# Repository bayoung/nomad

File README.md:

# Nomad

Keyboard for Digital Nomads

# Config and Build Firmware

* cd nomad
* git clone git@github.com:bayoung/qmk_firmware.git
* git checkout brian.young/nomad
* cd qmk_firmware
* git submodule sync --recursive
* git submodule update --init --recursive --progress
* make nomad:default
* run teensy.app
* select qmk_firmware/nomad_default.hex
* press reset on Keyboard (or Fn-Esc if there's good firmware running)
* load
* replug USB cable on keyboard

# PCB

* cd pcb
* git clone git@github.com:keebio/Keebio-Parts.pretty.git
* cd Keebio-Parts.pretty
* git checkout aec652e40624d7872b2659f307ac483922ba315f
* cd ..
* git clone git@github.com:XenGi/teensy_library.git
* git checkout 14f5629c7d822ed95580319626f745de2a11fefd
* cd ..
* open NomadLeft / NomadRight in KiCad

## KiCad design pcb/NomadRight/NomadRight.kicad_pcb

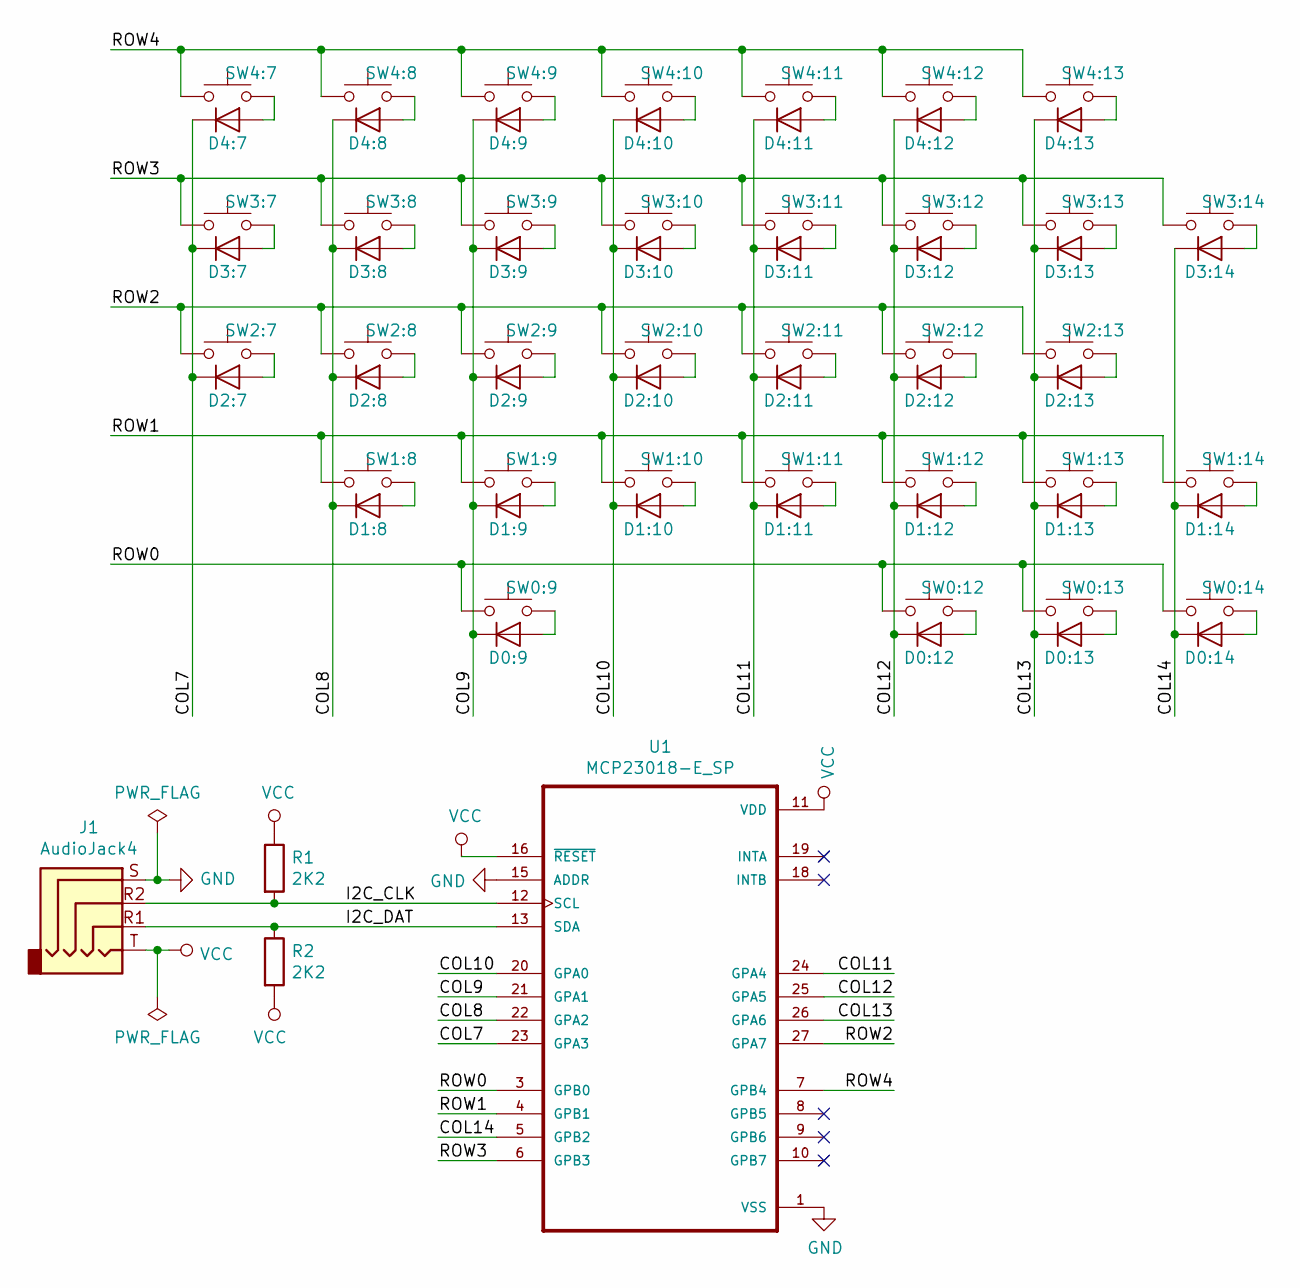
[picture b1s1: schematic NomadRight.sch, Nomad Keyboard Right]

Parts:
D0:9, D0:12, D0:13, D0:14, D1:8, D1:9, D1:10, D1:11, D1:12, D1:13, D1:14, D2:7, D2:8, D2:9, D2:10, D2:11, D2:12, D2:13, D3:7, D3:8, D3:9, D3:10, D3:11, D3:12, D3:13, D3:14, D4:7, D4:8, D4:9, D4:10, D4:11, D4:12, D4:13: 1N4148TR; D_DO-35_SOD27_P7.62mm_Horizontal
J1: AudioJack4; CUI_SJ-43514
R1, R2: 2K2; R_0805_2012Metric_Pad1.15x1.40mm_HandSolder
SW0:9, SW0:12, SW0:13, SW0:14, SW1:8, SW1:9, SW1:10, SW1:11, SW1:12, SW1:13, SW1:14, SW2:7, SW2:8, SW2:9, SW2:10, SW2:11, SW2:12, SW2:13, SW3:7, SW3:8, SW3:9, SW3:10, SW3:11, SW3:12, SW3:13, SW3:14, SW4:7, SW4:8, SW4:9, SW4:10, SW4:11, SW4:12, SW4:13: SW_Push; Kailh-PG1350-1u
U1: MCP23018-E_SP; DIP-28_W7.62mm

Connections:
/COL7: D2:7.1 (K), D3:7.1 (K), D4:7.1 (K), U1.23 (GPA3)
/COL8: D1:8.1 (K), D2:8.1 (K), D3:8.1 (K), D4:8.1 (K), U1.22 (GPA2)
/COL9: D0:9.1 (K), D1:9.1 (K), D2:9.1 (K), D3:9.1 (K), D4:9.1 (K), U1.21 (GPA1)
/COL10: D1:10.1 (K), D2:10.1 (K), D3:10.1 (K), D4:10.1 (K), U1.20 (GPA0)
/COL11: D1:11.1 (K), D2:11.1 (K), D3:11.1 (K), D4:11.1 (K), U1.24 (GPA4)
/COL12: D0:12.1 (K), D1:12.1 (K), D2:12.1 (K), D3:12.1 (K), D4:12.1 (K), U1.25 (GPA5)
/COL13: D0:13.1 (K), D1:13.1 (K), D2:13.1 (K), D3:13.1 (K), D4:13.1 (K), U1.26 (GPA6)
/COL14: D0:14.1 (K), D1:14.1 (K), D3:14.1 (K), U1.5 (GPB2)
/I2C_CLK: J1.R2, R1.2, U1.12 (SCL)
/I2C_DAT: J1.R1, R2.1, U1.13 (SDA)
/ROW0: SW0:9.1, SW0:12.1, SW0:13.1, SW0:14.1, U1.3 (GPB0)
/ROW1: SW1:8.1, SW1:9.1, SW1:10.1, SW1:11.1, SW1:12.1, SW1:13.1, SW1:14.1, U1.4 (GPB1)
/ROW2: SW2:7.1, SW2:8.1, SW2:9.1, SW2:10.1, SW2:11.1, SW2:12.1, SW2:13.1, U1.27 (GPA7)
/ROW3: SW3:7.1, SW3:8.1, SW3:9.1, SW3:10.1, SW3:11.1, SW3:12.1, SW3:13.1, SW3:14.1, U1.6 (GPB3)
/ROW4: SW4:7.1, SW4:8.1, SW4:9.1, SW4:10.1, SW4:11.1, SW4:12.1, SW4:13.1, U1.7 (GPB4)
GND: J1.S, U1.1 (VSS), U1.15 (ADDR)
unnamed: D0:9.2 (A), SW0:9.2
unnamed: D0:12.2 (A), SW0:12.2
unnamed: D0:13.2 (A), SW0:13.2
unnamed: D0:14.2 (A), SW0:14.2
unnamed: D1:8.2 (A), SW1:8.2
unnamed: D1:9.2 (A), SW1:9.2
unnamed: D1:10.2 (A), SW1:10.2
unnamed: D1:11.2 (A), SW1:11.2
unnamed: D1:12.2 (A), SW1:12.2
unnamed: D1:13.2 (A), SW1:13.2
unnamed: D1:14.2 (A), SW1:14.2
unnamed: D2:7.2 (A), SW2:7.2
unnamed: D2:8.2 (A), SW2:8.2
unnamed: D2:9.2 (A), SW2:9.2
unnamed: D2:10.2 (A), SW2:10.2
unnamed: D2:11.2 (A), SW2:11.2
unnamed: D2:12.2 (A), SW2:12.2
unnamed: D2:13.2 (A), SW2:13.2
unnamed: D3:7.2 (A), SW3:7.2
unnamed: D3:8.2 (A), SW3:8.2
unnamed: D3:9.2 (A), SW3:9.2
unnamed: D3:10.2 (A), SW3:10.2
unnamed: D3:11.2 (A), SW3:11.2
unnamed: D3:12.2 (A), SW3:12.2
unnamed: D3:13.2 (A), SW3:13.2
unnamed: D3:14.2 (A), SW3:14.2
unnamed: D4:7.2 (A), SW4:7.2
unnamed: D4:8.2 (A), SW4:8.2
unnamed: D4:9.2 (A), SW4:9.2
unnamed: D4:10.2 (A), SW4:10.2
unnamed: D4:11.2 (A), SW4:11.2
unnamed: D4:12.2 (A), SW4:12.2
unnamed: D4:13.2 (A), SW4:13.2
VCC: J1.T, R1.1, R2.2, U1.11 (VDD), U1.16 (~RESET~)

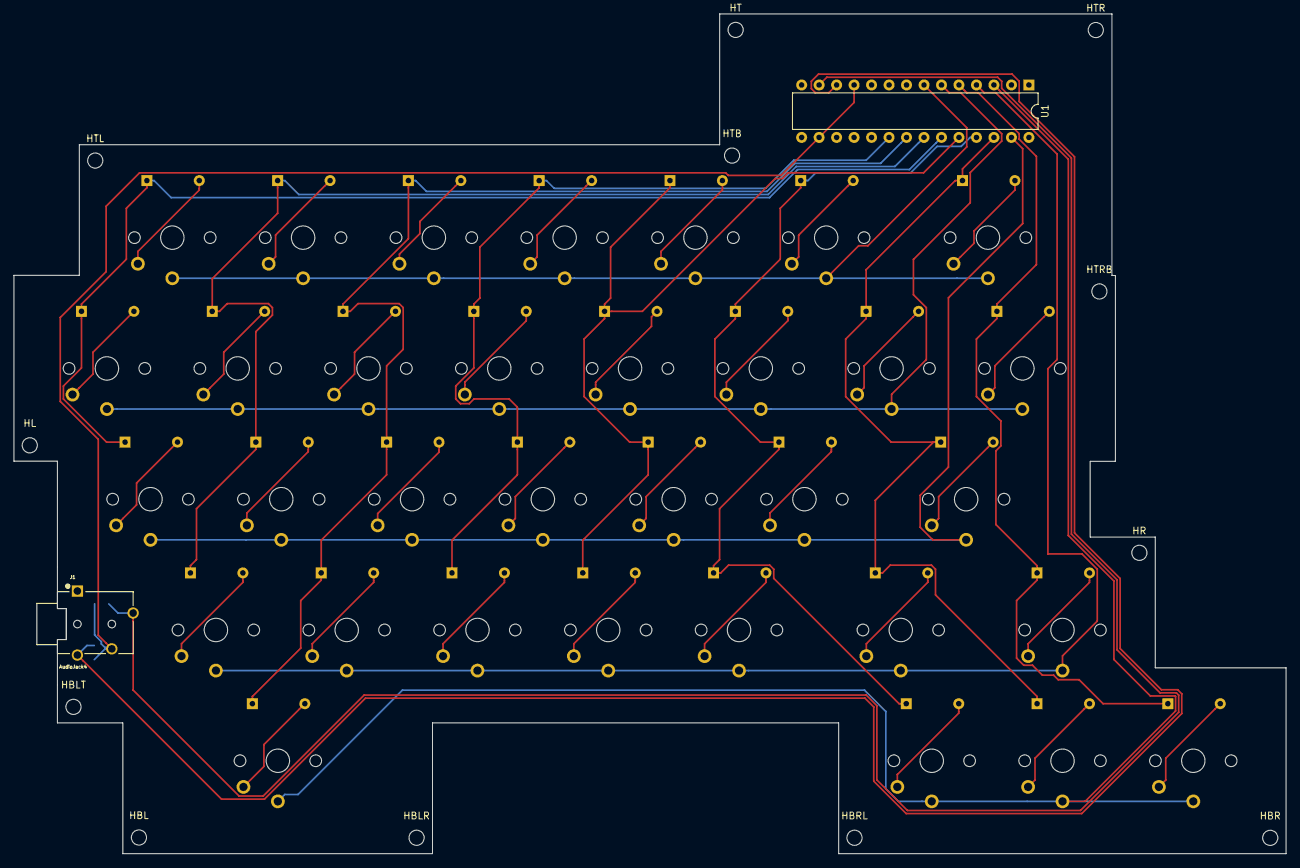
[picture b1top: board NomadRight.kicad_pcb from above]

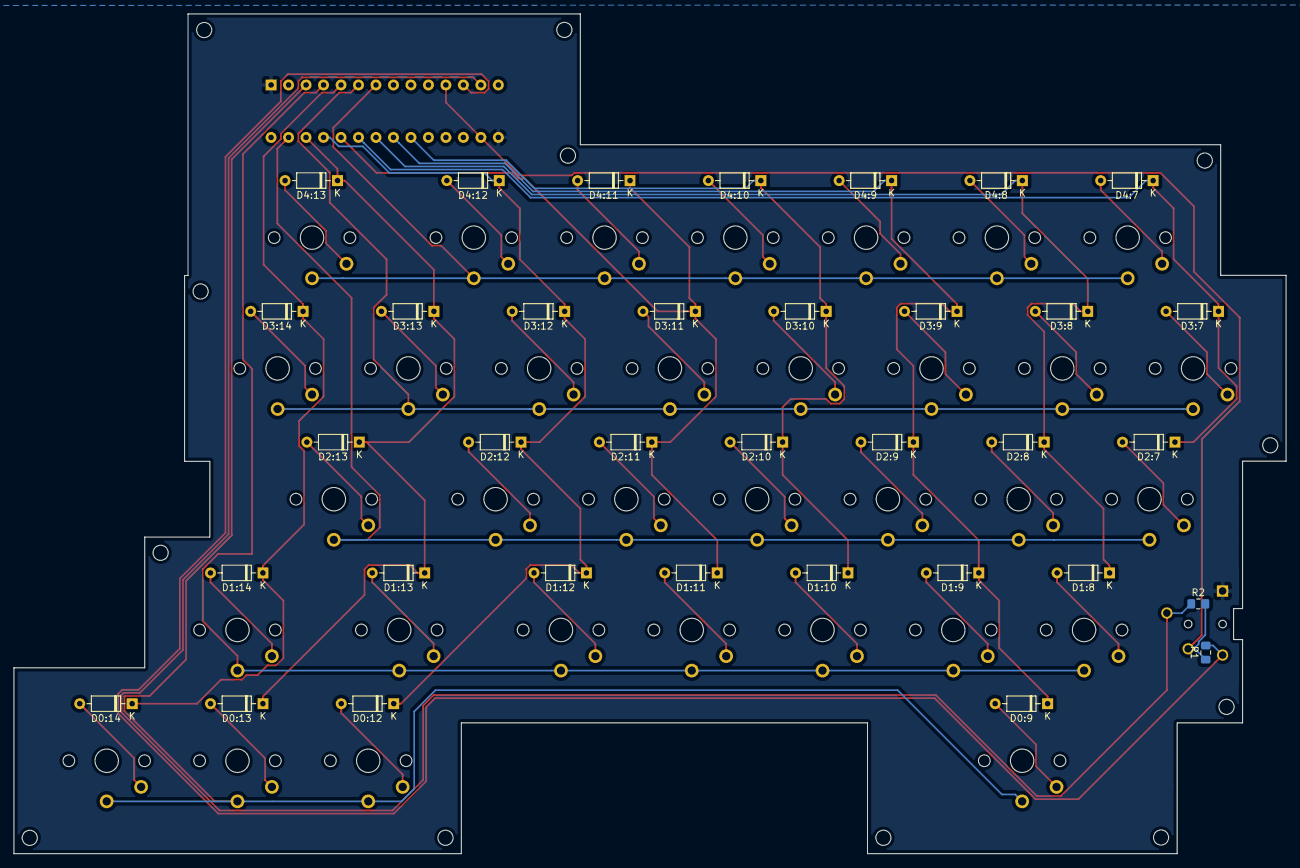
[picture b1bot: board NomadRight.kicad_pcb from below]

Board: 2 copper layers, 184.8 x 122.0 mm, 82 parts (35 on the bottom side), 50 nets.

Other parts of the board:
HBL: MountingHole_2.2mm_M2
HBLR: MountingHole_2.2mm_M2
HBLT: MountingHole_2.2mm_M2
HBR: MountingHole_2.2mm_M2
HBRL: MountingHole_2.2mm_M2
HL: MountingHole_2.2mm_M2
HR: MountingHole_2.2mm_M2
HT: MountingHole_2.2mm_M2
HTB: MountingHole_2.2mm_M2
HTL: MountingHole_2.2mm_M2
HTR: MountingHole_2.2mm_M2
HTRB: MountingHole_2.2mm_M2

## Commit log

2020-09-20 Ignore sub git repository for the firmware
2020-09-20 Firmware config and build instructions
2020-09-20 Add PCB files
2020-09-21 Mark Fusion files to use GitHub large file support.
2020-09-21 Fusion 360 model for the folding enclosure.
2020-10-26 Fix schematics by rescuing symbols.
